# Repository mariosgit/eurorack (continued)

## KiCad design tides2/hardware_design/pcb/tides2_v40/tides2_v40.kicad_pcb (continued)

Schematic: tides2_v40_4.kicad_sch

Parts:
C6, C17, C33, C34, C48, C49: 100n; C0402
C18, C21: 1u; C0402
C29: 10u; PANASONIC_A
C37, C38, C39, C40: 47p; C0402
IC4: DAC8564; SOP65P640X110-16N
IC8, IC9: TL074PW; TSSOP14_065
J9, J10, J11, J12: PJ301_THONKICONN6; WQP_PJ_301M6
LED4, LED5, LED6, LED7: LED-BICOLOR-SHARED-THROUGHHOLE; LED3MM
R14, R38, R39, R40, R42: 130k; R0402
R15: 100k; R0402
R31, R32, R33, R34: 20k; R0402
R45, R47, R48, R49: 1.0k; R0603
R64, R65, R66, R67: 1.0k; R0402

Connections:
+3V3: C6.1, IC4.12 (DVDD); also elsewhere on the board
+3V3_A: C17.1, C29.+, IC4.4 (AVDD); also elsewhere on the board
/tides2_v40_4/DAC_1: IC4.1 (OUTA), R31.2
/tides2_v40_4/DAC_2: IC4.2 (OUTB), R32.2
/tides2_v40_4/DAC_3: IC4.7 (OUTC), R33.2
/tides2_v40_4/DAC_4: IC4.8 (OUTD), R34.2
/tides2_v40_4/VREF: C18.1, IC4.3 (VREFH), R14.2
/tides2_v40_4/VREF_BIAS: C21.1, IC8.10 (+IN), IC8.12 (+IN), IC9.10 (+IN), IC9.12 (+IN), R14.1, R15.2
DAC_MOSI: IC4.11 (IN); also elsewhere on the board
DAC_SCK: IC4.10 (SCK); also elsewhere on the board
DAC_SS: IC4.9 (SYNC); also elsewhere on the board
GND: C6.2, C17.2, C18.2, C21.2, C29.-, C33.1, C34.1, C48.2, C49.2, IC4.5 (VREFL), IC4.6 (GND), IC4.13 (A0), IC4.14 (A1), IC4.15 (ENABLE), IC4.16 (LDAC), J9.P1 (1), J10.P1 (1), J11.P1 (1), J12.P1 (1), R15.1, R64.2, R65.2, R66.2, R67.2; also elsewhere on the board
unnamed: C39.2, IC8.3 (+IN), IC8.14 (OUT), R48.2
unnamed: IC8.2 (-IN), LED6.2, R66.1
unnamed: IC8.1 (OUT), LED6.1
unnamed: C40.2, IC8.5 (+IN), IC8.8 (OUT), R49.2
unnamed: IC8.6 (-IN), LED7.2, R67.1
unnamed: IC8.7 (OUT), LED7.1
unnamed: C40.1, IC8.9 (-IN), R34.1, R40.2
unnamed: C39.1, IC8.13 (-IN), R33.1, R39.2
unnamed: C37.2, IC9.3 (+IN), IC9.14 (OUT), R47.2
unnamed: IC9.2 (-IN), LED4.2, R64.1
unnamed: IC9.1 (OUT), LED4.1
unnamed: C38.2, IC9.5 (+IN), IC9.8 (OUT), R45.2
unnamed: IC9.6 (-IN), LED5.2, R65.1
unnamed: IC9.7 (OUT), LED5.1
unnamed: C38.1, IC9.9 (-IN), R32.1, R38.2
unnamed: C37.1, IC9.13 (-IN), R31.1, R42.2
unnamed: J9.P3 (3), R42.1, R47.1
unnamed: J10.P3 (3), R38.1, R45.1
unnamed: J11.P3 (3), R39.1, R48.1
unnamed: J12.P3 (3), R40.1, R49.1
VCC: C48.1, C49.1, IC8.4 (V+), IC9.4 (V+); also elsewhere on the board
VEE: C33.2, C34.2, IC8.11 (V-), IC9.11 (V-); also elsewhere on the board

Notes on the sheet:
-8.1V to 8.1V
Émilie Gillet
1.087V
DAC and outputs
emilie.o.gillet@gmail.com
cc-by-sa

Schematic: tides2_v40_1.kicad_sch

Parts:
C1, C12, C13, C16: 1u; C0402
C2, C3, C8, C14, C15: 100n; C0402
C4, C11: 20p; C0402
IC1: STM32F373C; LQFP48
JP6: M04PTH; 1X04
JP7: M02PTH; 1X02
Q1: CRYSTAL; CTS406
R3: 10k; R0402
R4, R5, R8, R9: 100; R0402

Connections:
+3V3: C1.1, C3.1, C15.1, C16.1, IC1.1 (VBAT), IC1.17 (VDD_2), IC1.48 (VDD_1), R3.1; also elsewhere on the board
+3V3_A: C8.1, C12.1, C13.1, C14.1, IC1.9 (VDDA), IC1.24 (VDDSD), IC1.25 (VREFSD+); also elsewhere on the board
/tides2_v40_1/RESET: C2.1, IC1.7 (NRST), JP6.4, R3.2
/tides2_v40_1/RX: IC1.46 (PB9/SPI2_NSS/I2S2_WS/I2C1_SDA/USART3_RX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), R4.2
/tides2_v40_1/SWCLK: IC1.37 (PA14/I2C1_SDA/JTCK-SWCLK), JP6.3
/tides2_v40_1/SWDIO: IC1.34 (PA13/SPI1_MISO/I2S1_MCK/USART3_CTS/TIM4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), JP6.2
/tides2_v40_1/TX: IC1.45 (PB8/SPI2_SCK/I2S2_CK/I2C1_SCL/USART3_TX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), R5.2
ADC_CLOCK: IC1.20 (PB2/SDADC1_AIN4P/SDADC2_AIN6P); also elsewhere on the board
ADC_FM: IC1.21 (PE8/SDADC1_AIN8P/SDADC2_AIN8P); also elsewhere on the board
ADC_SHAPE: IC1.27 (PB15/SPI2_MOSI/I2S2_SD/SDADC3_AIN7P/SDA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); also elsewhere on the board
ADC_SHIFT: IC1.28 (PD8/SPI2_SCK/I2S2_CK/USART3_TX/SDADC3_A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); also elsewhere on the board
ADC_SLOPE: IC1.18 (PB0/SPI1_MOSI/I2S1_SD/TIM3_CH3/ADC_IN8/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); also elsewhere on the board
ADC_SMOOTHNESS: IC1.26 (PB14/SPI2_MISO/I2S2_MCK/USART3_RTS/SDAD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); also elsewhere on the board
ADC_TRIG: IC1.19 (PB1/TIM3_CH4/ADC_IN9/SDADC1_AIN5P/SDADC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); also elsewhere on the board
ADC_V_OCT: IC1.22 (PE9/SDADC1_AIN7P/SDADC1_AIN8M/SDADC2_AI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); also elsewhere on the board
DAC_MOSI: IC1.31 (PA10/SPI2_MOSI/I2S2_SD/I2C2_SDA/USART1_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); also elsewhere on the board
DAC_SCK: IC1.29 (PA8/SPI2_SCK/I2S2_CK/I2C2_SMBA/USART1_C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); also elsewhere on the board
DAC_SS: IC1.32 (PA11/SPI2_NSS/I2S2_WS/SPI1_NSS/I2S1_WS/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); also elsewhere on the board
FREQUENCY_POT: IC1.16 (PA6/SPI1_MISO/I2S1_MCK/TIM3_CH1/ADC_IN6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); also elsewhere on the board
GND: C1.2, C2.2, C3.2, C4.1, C8.2, C11.1, C12.2, C13.2, C14.2, C15.2, C16.2, IC1.8 (VSSA), IC1.23 (VSSSD/VREFSD-), IC1.44 (BOOT0), IC1.47 (VSS_1), JP6.1, Q1.2 (LID1), Q1.4 (LID2); also elsewhere on the board
LED_MODE_G: IC1.35 (PF6/SPI1_MOSI/I2S1_SD/USART3_RTS/TIM4_C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); also elsewhere on the board
LED_MODE_R: IC1.36 (PF7/I2C2_SDA/USART2_CK); also elsewhere on the board
LED_RANGE_G: IC1.42 (PB6/I2C1_SCL/USART1_TX/TIM4_CH1); also elsewhere on the board
LED_RANGE_R: IC1.41 (PB5/SPI1_MOSI/I2S1_SD/SPI3_MOSI/I2S3_SD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); also elsewhere on the board
LED_SHIFT_G: IC1.40 (PB4/SPI1_MISO/I2S1_MCK/SPI3_MISO/I2S3_M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); also elsewhere on the board
LED_SHIFT_R: IC1.39 (PB3/SPI1_SCK/I2S1_CK/SPI3_SCK/I2S3_CK/U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); also elsewhere on the board
MUXED_POTS: IC1.11 (PA1/SPI3_SCK/I2S3_CK/USART2_RTS/TIM2_CH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); also elsewhere on the board
MUX_ADDR_0: IC1.13 (PA3/SPI3_MOSI/I2S3_SD/USART2_RX/TIM2_CH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); also elsewhere on the board
MUX_ADDR_1: IC1.14 (PA4/SPI1_NSS/I2S1_WS/SPI3_NSS/I2S3_WS/U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); also elsewhere on the board
MUX_ADDR_2: IC1.15 (PA5/SPI1_SCK/I2S1_CK/TIM2_CH1/ADC_IN5/D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); also elsewhere on the board
NORMALIZATION_PROBE: IC1.30 (PA9/SPI_MISO/I2S2_MCK/I2C2_SCL/USART1_T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); also elsewhere on the board
unnamed: C11.2, Q1.1, R9.2
unnamed: IC1.5 (PF0/OSC_IN/I2C2_SDA), R8.1
unnamed: IC1.6 (PF1/OSC_OUT/I2C2_SCL), R9.1
unnamed: JP7.1, R4.1
unnamed: JP7.2, R5.1
unnamed: C4.2, Q1.3 (2), R8.2
SHAPE_POT: IC1.10 (PA0/USART2_CTS/TIM2_CH1/TIM5_CH1/ADC_IN0); also elsewhere on the board
SW_MODE: IC1.33 (PA12/SPI1_SCK/I2S1_CK/USART1_RTS/CAN_TX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); also elsewhere on the board
SW_RANGE: IC1.12 (PA2/SPI3_MISO/I2S3_MCK/USART2_TX/TIM2_C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); also elsewhere on the board
SW_SHIFT: IC1.2 (PC13/TIMESTAMP/RTC_TAMPER1); also elsewhere on the board

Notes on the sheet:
cc-by-sa
MCU
Émilie Gillet
emilie.o.gillet@gmail.com

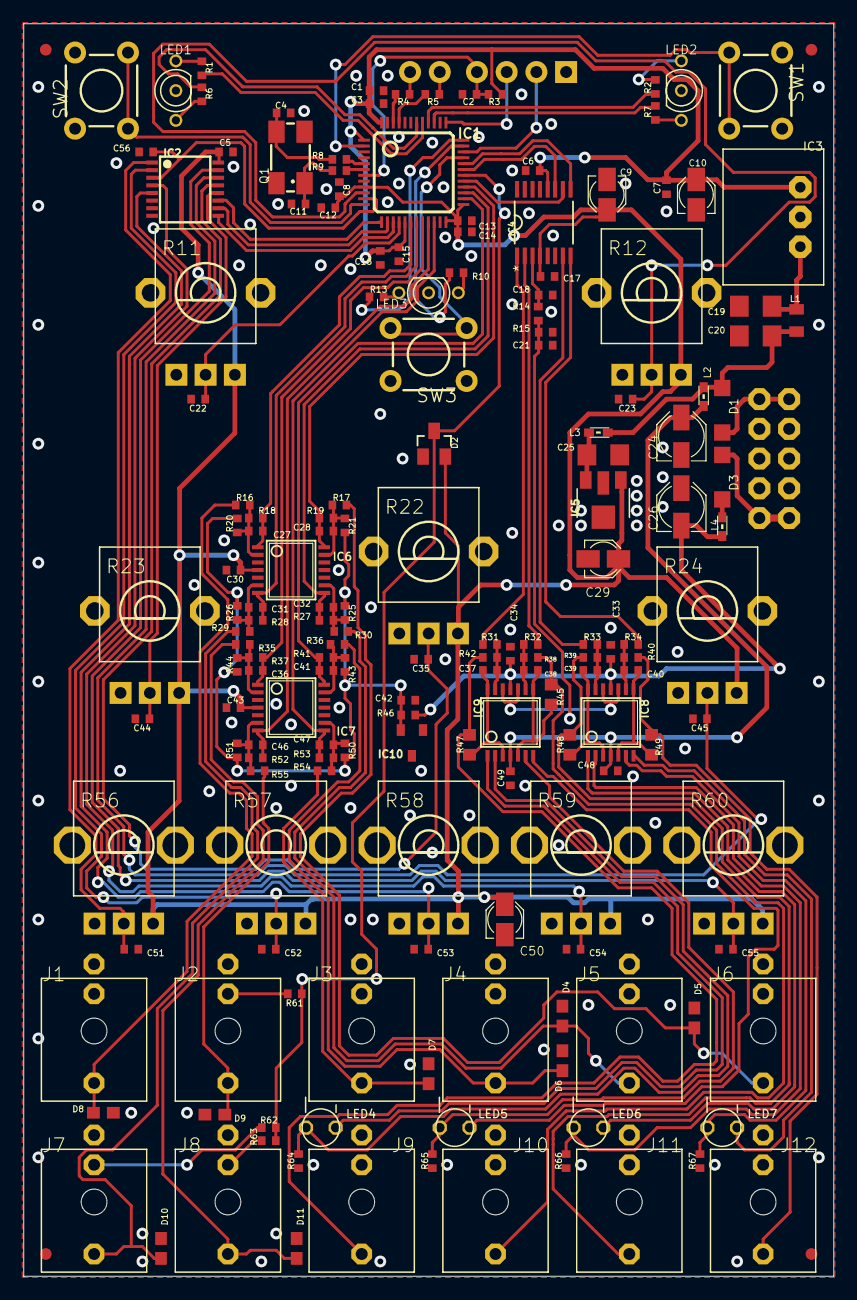
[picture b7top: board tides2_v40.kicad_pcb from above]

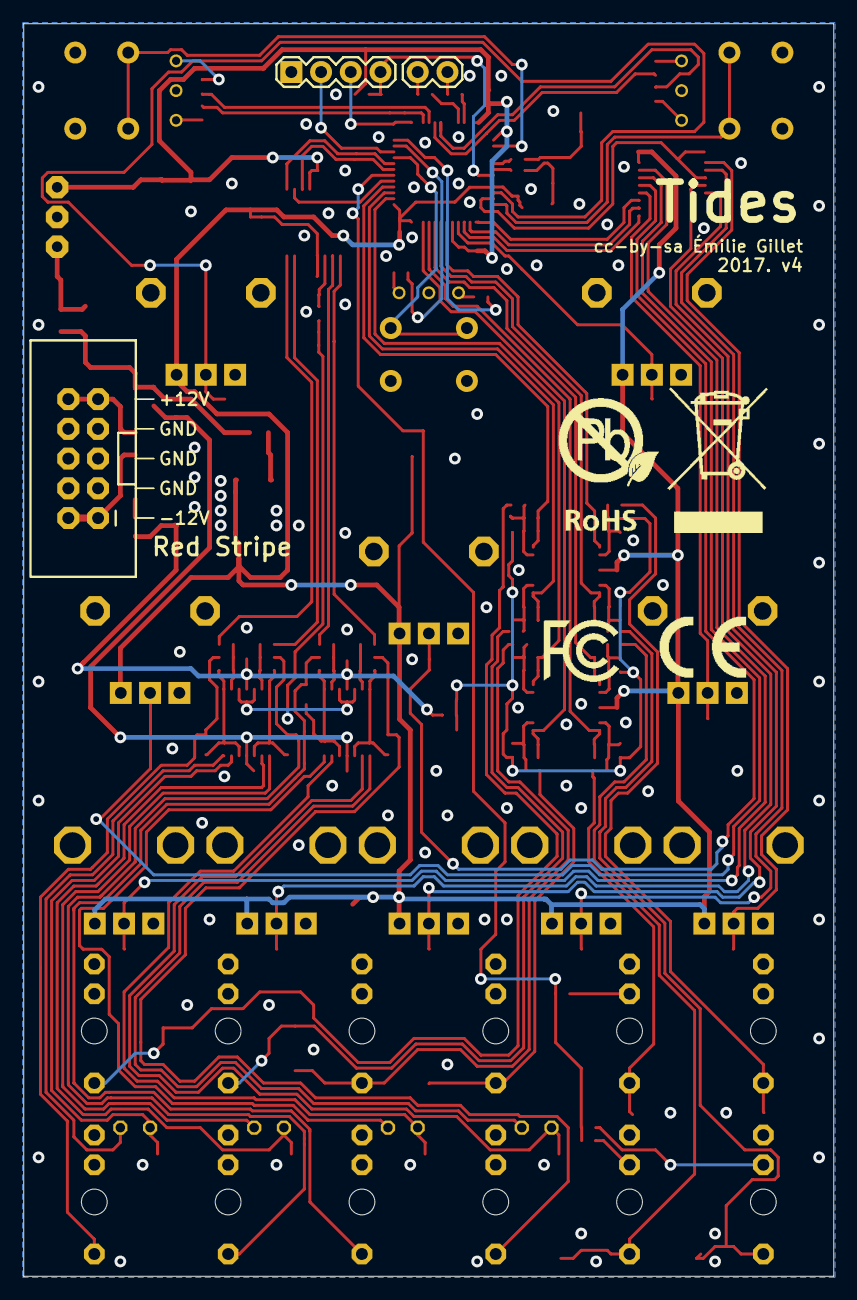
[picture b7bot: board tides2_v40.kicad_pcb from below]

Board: 2 copper layers, 69.2 x 107.0 mm, 181 parts (6 on the bottom side), 109 nets.

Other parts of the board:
U$2: ROHS_BIG
U$4: CE_MEDIUM
U$5: FCC_MEDIUM

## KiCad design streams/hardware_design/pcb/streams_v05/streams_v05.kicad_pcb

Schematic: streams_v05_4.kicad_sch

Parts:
C1, C13, C17, C47, C56: 100n; C0603
C2, C24, C28: 10u; PANASONIC_B
C11: 22u; PANASONIC_B
C16: 22u; PANASONIC_C
D3, D6: 1N5819HW; SOD123
IC2: REG1117; SOT223
IC3, IC11, IC12: LM4041DBZ; DBZ_R-PDSO-G3
JP6: M05X2PTH; AVR_ICSP
L1: WE-CBF_0603; 0603
P1: PTCSMD; PTC-1206
R8, R57: 3.3k; R0603
R11: 4.7; R1206
R46: 1.0k; R0603

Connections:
+3V3: C11.+, C13.1, IC2.2 (VOUT), L1.1; also elsewhere on the board
+3V3_A: C1.1, C2.+, L1.2, R8.1; also elsewhere on the board
AREF_2.5: C17.1, IC3.1 (C), R8.2; also elsewhere on the board
AREF_+10: C56.1, IC12.1 (C), R57.2; also elsewhere on the board
AREF_-10: C47.1, IC11.2 (A), R46.2; also elsewhere on the board
GND: C1.2, C2.-, C11.-, C13.2, C16.-, C17.2, C24.-, C28.+, C47.2, C56.2, D6.C, IC2.1 (GND), IC3.2 (A), IC11.1 (C), IC12.2 (A), JP6.3, JP6.4, JP6.5, JP6.6, JP6.7, JP6.8; also elsewhere on the board
unnamed: C16.+, IC2.3 (VIN), R11.2
unnamed: D3.A, JP6.1, JP6.2
unnamed: JP6.9, JP6.10, P1.2
VCC: C24.+, D3.C, R11.1, R57.1; also elsewhere on the board
VEE: C28.-, D6.A, P1.1, R46.1; also elsewhere on the board

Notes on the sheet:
Wurth 742792693
emilie.o.gillet@gmail.com
160µA
Émilie Gillet
150µA
500µA
cc-by-sa
Power supply

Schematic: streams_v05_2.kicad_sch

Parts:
C18, C26: 1.0n; C0603
C25, C35, C41, C44, C46, C48, C49: 100n; C0603
C30, C40, C53: 33p; C0603
C36, C38, C50, C54: 560p; C0603
D1: BAT54S; SOT23
D5: 1N4148; SOD323-W
IC4: TL074D; SO14
IC5, IC7: TL072D; SO08
IC8: SSM2164S; SOIC16N
J1, J2, J5, J6: PJ301WQP; WQP_PJ_301BM_WIDER
R6, R61: 1.0k; R0603
R9, R26: 120k; R0603
R12, R25, R34, R42, R49, R51, R52, R59: 100k; R0603
R18, R22: 20k; R0603
R27: 4025UB103; ALPS_POT_VERTICAL
R30: 14k; R0603
R31, R38, R41, R47, R50: 510; R0603
R32: 50kB; ALPS_POT_VERTICAL_PS
R37: 200k; R0603
R60: 24.9k; R0603
R65: 10M; R0603
TP1: TEST-POINT3X5; PAD.03X.05

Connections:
+3V3_A: C25.1, D1.2 (C), IC4.4 (V+); also elsewhere on the board
ADC_AUX_1: C26.2, IC4.1 (OUT), R22.2; also elsewhere on the board
ADC_CV_1: D1.3 (AC), R6.1; also elsewhere on the board
ADC_IN_1: C18.2, IC4.14 (OUT), R18.2; also elsewhere on the board
AREF_+5: J2.SW (3), R59.1
AREF_+10: R59.2, R60.2; also elsewhere on the board
AREF_-10: R9.1, R26.1, R37.1, R65.1; also elsewhere on the board
DAC_1: R30.1; also elsewhere on the board
FB_CURRENT1: IC8.10 (IN), R37.2, R38.2
FB_CURRENT2: IC8.15 (IN), R41.2, R42.2
GND: C25.2, C35.2, C36.2, C38.2, C41.2, C44.1, C46.2, C48.1, C49.1, C50.2, C54.2, D1.1 (A), D5.A, IC4.3 (+IN), IC4.11 (V-), IC4.12 (+IN), IC5.3 (+IN), IC5.5 (+IN), IC7.3 (+IN), IC7.5 (+IN), IC8.8 (GND), J1.GND (1), J1.GND2 (4), J2.GND (1), J2.GND2 (4), J5.GND (1), J5.GND2 (4), J6.GND (1), J6.GND2 (4), R31.1, R32.P$3 (A); also elsewhere on the board
IN_1: J2.TIP (2), R12.1, R42.1
unnamed: R27.P$3 (A), R31.2
unnamed: C30.1, IC5.6 (-IN), IC8.12 (OUT), R30.2, R32.P$1 (E), R65.2
unnamed: C38.1, R38.1
unnamed: C36.1, R41.1
unnamed: IC5.1 (OUT), IC5.2 (-IN)
unnamed: J5.SW (3), R60.1
unnamed: J5.TIP (2), R34.1
unnamed: IC8.11 (CTRL), R27.P$2 (S)
unnamed: R32.P$2 (S), R34.2
unnamed: C40.1, IC7.6 (-IN), IC8.5 (OUT)
unnamed: C40.2, IC7.7 (OUT), R52.2, R61.1
unnamed: IC8.2 (IN), IC8.13 (OUT), R49.1, R50.2
unnamed: J1.TIP (2), R25.1
unnamed: C18.1, IC4.13 (-IN), R9.2, R12.2, R18.1
unnamed: C26.1, IC4.2 (-IN), R22.1, R25.2, R26.2
unnamed: C53.1, IC7.2 (-IN), IC8.4 (OUT)
unnamed: C53.2, IC7.1 (OUT), R49.2, R51.1
unnamed: IC8.7 (IN), R47.2, R51.2, R52.1
unnamed: C54.1, R50.1
unnamed: C50.1, R47.1
unnamed: J6.TIP (2), R61.2
PWM_CUTOFF_1: IC8.3 (CTRL), IC8.6 (CTRL); also elsewhere on the board
VCA_CONTROL_1: C30.2, D5.C, IC5.7 (OUT), IC8.14 (CTRL), R6.2, R27.P$1 (E), TP1.P$1
VCC: C35.1, C41.1, C46.1, IC5.8 (V+), IC7.8 (V+), IC8.16 (V+); also elsewhere on the board
VEE: C44.2, C48.2, C49.2, IC5.4 (V-), IC7.4 (V-), IC8.9 (V-); also elsewhere on the board

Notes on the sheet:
cc-by-sa
Channel 1
+11k load from filter
Émilie Gillet
emilie.o.gillet@gmail.com

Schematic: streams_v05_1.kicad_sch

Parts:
C3, C4, C8, C10, C14: 100n; C0603
C5, C12: 18p; C0603
C6, C7: 680n; C0603
C9, C15: 3.3u; C0603
C20, C21: 10n; C0603
C22, C23: 1.0n; C0603
IC1: DAC8552; MSOP-8
JP1, JP2, JP4, JP5: FIDUCIAL1X2; FIDUCIAL-1X2
JP3: M03X2BOTTOM; 2X3_BOTTOM
JP7: M05X2MINIJTAG; 2X5-1.27
Q1: 8MHz; HC49UP
R1, R20, R21: 10k; R0603
R2, R3, R14, R15: 10kB; ALPS_POT_VERTICAL_PS
R4, R5: 1.2k; R0603
R16, R17: 1.0k; R0603
SW1, SW2, SW3: TAC_SWITCHPTH; TACTILE-PTH
UC1: STM32F103CB; LQFP48

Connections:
+3V3: C3.1, C4.1, C10.1, JP3.4, JP3.6, JP7.1, R1.2, UC1.1 (VBAT), UC1.24 (VDD_1), UC1.36 (VDD_2), UC1.48 (VDD_3); also elsewhere on the board
+3V3_A: C8.1, C9.1, C14.1, C15.1, IC1.1 (VDD), R2.P$1 (E), R3.P$1 (E), R14.P$1 (E), R15.P$1 (E), UC1.9 (VDD_A); also elsewhere on the board
ADC_AUX_1: UC1.18 (PB0/ADC12_IN8/TIM3_CH3); also elsewhere on the board
ADC_AUX_2: UC1.16 (PA6/SPI1_MISO/ADC12_IN6/TIM3_CH1); also elsewhere on the board
ADC_CV_1: UC1.14 (PA4/SPI1_NSS/USART2_CK/ADC12_IN4); also elsewhere on the board
ADC_CV_2: UC1.15 (PA5/SPI1_SCK/ADC12_IN5); also elsewhere on the board
ADC_IN_1: UC1.17 (PA7/SPI1_MOSI/ADC12_IN7/TIM3_CH2); also elsewhere on the board
ADC_IN_2: UC1.19 (PB1/ADC12_IN9/TIM3_CH4); also elsewhere on the board
AMOUNT_1: R14.P$2 (S), UC1.13 (PA3/USART2_RX/ADC12_IN3/TIM2_CH4)
AMOUNT_2: R15.P$2 (S), UC1.10 (PA0_WKUP/USART2_CTS/ADC12_IN0/TIM2_CH1_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)
AREF_2.5: IC1.2 (VREF); also elsewhere on the board
BARGRAPH_CS: JP3.5, UC1.43 (PB7/I2C1_SDA/TIM4_CH2)
BARGRAPH_MOSI: JP3.1, UC1.21 (PB10/I2C2_SCL/USART3_TX)
BARGRAPH_SCK: JP3.3, UC1.22 (PB11/I2C2_SDA/USART3_RX)
DAC_1: C22.1, R20.2; also elsewhere on the board
DAC_2: C23.1, R21.2; also elsewhere on the board
DAC_MOSI: IC1.7 (DIN), UC1.28 (PB15/SPI2_MOSI/TIM1_CH3N)
DAC_SCK: IC1.6 (SCLK), UC1.26 (PB13/SPI2_SCK/USART3_CTS/TIM1_CH1N)
DAC_SS: IC1.5 (~SYNC), UC1.25 (PB12/SPI2_NSS/I2C2_SMBA/USART3_CK/TIM1_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)
GND: C3.2, C4.2, C5.1, C6.2, C7.2, C8.2, C9.2, C10.2, C12.1, C14.2, C15.2, C20.2, C21.2, C22.2, C23.2, IC1.8 (GND), JP3.2, JP7.3, JP7.5, JP7.9, R2.P$3 (A), R3.P$3 (A), R14.P$3 (A), R15.P$3 (A), SW1.1, SW1.2, SW2.1, SW2.2, SW3.1, SW3.2, UC1.8 (VSS_A), UC1.20 (PB2/BOOT1), UC1.23 (VSS_1), UC1.35 (VSS_2), UC1.44 (BOOT0), UC1.47 (VSS_3); also elsewhere on the board
JTCK: JP7.4, UC1.37 (PA14/JTCK/SWCLK)
JTDI: JP7.8, UC1.38 (PA15/JTDI)
JTDO: JP7.6, UC1.39 (PB3/JTDO)
JTMS: JP7.2, UC1.34 (PA13/JTMS/SWDIO)
unnamed: C5.2, Q1.2, UC1.5 (PD0-OSC_IN)
unnamed: C12.2, Q1.1, UC1.6 (PD1-OSC_OUT)
unnamed: IC1.4 (OUTA), R17.1
unnamed: IC1.3 (OUTB), R16.1
unnamed: C21.1, R17.2, R21.1
unnamed: C20.1, R16.2, R20.1
unnamed: R5.1, UC1.32 (PA11/USART1_CTS/CAN_RX/TIM1_CH4/USBDM)
unnamed: R4.1, UC1.31 (PA10/USART1_RX/TIM1_CH3)
PWM_CUTOFF_1: C6.1, R4.2; also elsewhere on the board
PWM_CUTOFF_2: C7.1, R5.2; also elsewhere on the board
RESET: JP7.10, R1.1, UC1.7 (NRST)
SHAPE_1: R2.P$2 (S), UC1.12 (PA2/USART2_TX/ADC12_IN2/TIM2_CH3)
SHAPE_2: R3.P$2 (S), UC1.11 (PA1/USART2_RTS/ADC12_IN1/TIM2_CH2)
SW_METER: SW3.3, SW3.4, UC1.42 (PB6/I2C1_SCL/TIM4_CH1)
SW_MODE_1: SW1.3, SW1.4, UC1.41 (PB5/I2C1_SMBA)
SW_MODE_2: SW2.3, SW2.4, UC1.40 (PB4/NJTRST)

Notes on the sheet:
Émilie Gillet
emilie.o.gillet@gmail.com
Digital section
cc-by-sa
mini JTAG

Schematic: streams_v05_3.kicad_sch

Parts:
C19, C27: 1.0n; C0603
C29, C32, C33, C34, C39, C45: 100n; C0603
C31, C43, C52: 33p; C0603
C37, C42, C51, C55: 560p; C0603
D2: BAT54S; SOT23
D4: 1N4148; SOD323-W
IC4: TL074D; SO14
IC6, IC10: TL072D; SO08
IC9: SSM2164S; SOIC16N
J3, J4, J7, J8: PJ301WQP; WQP_PJ_301BM_WIDER
R7, R62: 1.0k; R0603
R10, R24: 120k; R0603
R13, R28, R35, R39, R53, R54, R56, R58: 100k; R0603
R19, R23: 20k; R0603
R29: 14k; R0603
R33: 50kB; ALPS_POT_VERTICAL_PS
R36: 4025UB103; ALPS_POT_VERTICAL
R40, R43, R45, R48, R55: 510; R0603
R44: 200k; R0603
R63: 24.9k; R0603
R64: 10M; R0603
TP2: TEST-POINT3X5; PAD.03X.05

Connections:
+3V3_A: D2.2 (C); also elsewhere on the board
ADC_AUX_2: C27.2, IC4.7 (OUT), R23.2; also elsewhere on the board
ADC_CV_2: D2.3 (AC), R7.1; also elsewhere on the board
ADC_IN_2: C19.2, IC4.8 (OUT), R19.2; also elsewhere on the board
AREF_+10: R58.2, R63.2; also elsewhere on the board
AREF_-10: R10.1, R24.1, R44.1, R64.1; also elsewhere on the board
DAC_2: R29.1; also elsewhere on the board
FB_CURRENT3: IC9.10 (IN), R39.2, R40.2
FB_CURRENT4: IC9.15 (IN), R43.2, R44.2
GND: C29.2, C32.2, C33.1, C34.1, C37.2, C39.1, C42.2, C45.2, C51.2, C55.2, D2.1 (A), D4.A, IC4.5 (+IN), IC4.10 (+IN), IC6.3 (+IN), IC6.5 (+IN), IC9.8 (GND), IC10.3 (+IN), IC10.5 (+IN), J3.GND (1), J3.GND2 (4), J4.GND (1), J4.GND2 (4), J7.GND (1), J7.GND2 (4), J8.GND (1), J8.GND2 (4), R33.P$3 (A), R45.1; also elsewhere on the board
IN_2: J3.TIP (2), R13.1, R39.1
unnamed: J8.SW (3), R63.1
unnamed: C37.1, R40.1
unnamed: C31.1, IC6.6 (-IN), IC9.13 (OUT), R29.2, R33.P$1 (E), R64.2
unnamed: C43.1, IC9.4 (OUT), IC10.6 (-IN)
unnamed: C43.2, IC10.7 (OUT), R53.2, R62.1
unnamed: J7.TIP (2), R62.2
unnamed: R36.P$3 (A), R45.2
unnamed: C42.1, R43.1
unnamed: R33.P$2 (S), R35.2
unnamed: J8.TIP (2), R35.1
unnamed: IC6.1 (OUT), IC6.2 (-IN)
unnamed: IC9.14 (CTRL), R36.P$2 (S)
unnamed: J3.SW (3), R58.1
unnamed: C27.1, IC4.6 (-IN), R23.1, R24.2, R28.2
unnamed: J4.TIP (2), R28.1
unnamed: C19.1, IC4.9 (-IN), R10.2, R13.2, R19.1
unnamed: IC9.7 (IN), IC9.12 (OUT), R55.2, R56.1
unnamed: C52.1, IC9.5 (OUT), IC10.2 (-IN)
unnamed: IC9.2 (IN), R48.2, R53.1, R54.2
unnamed: C52.2, IC10.1 (OUT), R54.1, R56.2
unnamed: C55.1, R55.1
unnamed: C51.1, R48.1
PWM_CUTOFF_2: IC9.3 (CTRL), IC9.6 (CTRL); also elsewhere on the board
VCA_CONTROL_2: C31.2, D4.C, IC6.7 (OUT), IC9.11 (CTRL), R7.2, R36.P$1 (E), TP2.P$1
VCC: C29.1, C32.1, C45.1, IC6.8 (V+), IC9.16 (V+), IC10.8 (V+); also elsewhere on the board
VEE: C33.2, C34.2, C39.2, IC6.4 (V-), IC9.9 (V-), IC10.4 (V-); also elsewhere on the board

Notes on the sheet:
Channel 2
Émilie Gillet
emilie.o.gillet@gmail.com
+11k load from filter
cc-by-sa

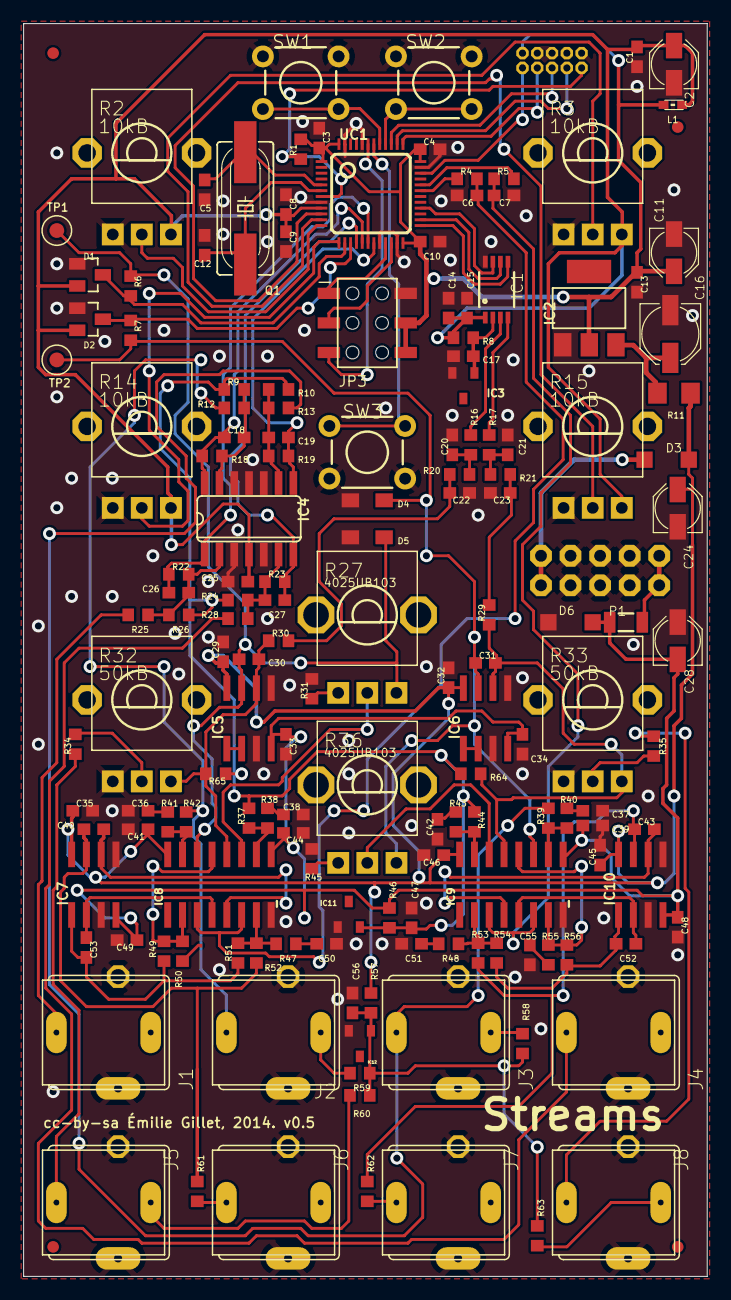
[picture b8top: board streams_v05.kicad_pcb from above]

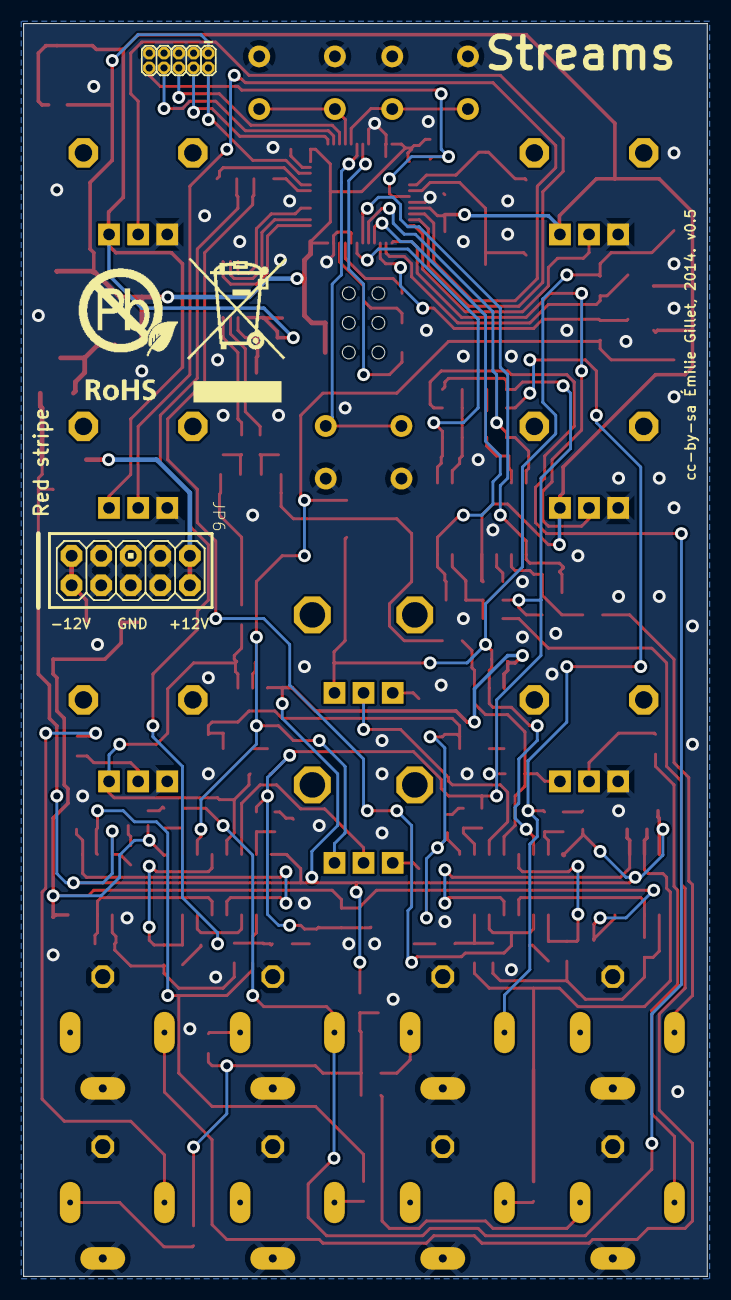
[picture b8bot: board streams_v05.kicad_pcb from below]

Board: 2 copper layers, 58.7 x 107.6 mm, 163 parts (3 on the bottom side), 98 nets.

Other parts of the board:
U$1: ROHS_BIG

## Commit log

2020-01-28 grids: changed Plug PM301 footprint, Switch enhanced to Multimec 3FTH9, added parts for MIDI in (not testet)
2020-01-28 stages: changed Poti-LED resistor values from 15k to 150
2020-01-28 howto build reminder for myself
2020-02-04 converting mini packages to 603
2020-02-06 converting mini packages to 603, all done, CRC check ok.
2020-02-15 more build reminders
2020-02-17 updated Plaits BOM with 0603 parts
2020-02-17 marbles -> 0603 pcb done
2020-03-13 marbles bom 603 update
2020-03-13 using older arm c++ 4.8.3 (elements had problems with audio timing)
2020-04-29 Minor stuff..
2020-04-29 Documented my changes.
2020-06-28 Added some signal text, this one works.
2020-06-28 Fixed Collision of c28 with POT, tested ok.
2023-03-20 All PCBs converted to v6, making it KiCad-readable.
2023-04-04 KiCadified branches,shelves,streams.
2023-04-05 Added submodul for kicad libs
2023-04-05 ..shelves kicad..
2023-04-05 tides2 kicadified
2023-05-04 edges->kicad
2023-05-04 refined edges kicad
2023-05-08 Edges pcb optimzed a little
2023-05-09 cleaned up blades dir
2023-05-09 Blades prod info xlsx's
2023-05-09 preped shelves kicad
2023-05-16 Added build instructions for WSL/Docker on Windows
2024-11-14 braids kicad version
2024-11-14 minor
2024-12-07 Blades rprodrun and some more kicad conversion
